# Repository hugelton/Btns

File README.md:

# Btns
Buttons board compatible with monome grid

## Overview
Btns is a clone of [Monome Grid]([url](https://monome.org)).

**⚠️ It doesn't support 16 levels of LED grey scale. It just turns on or off. **

## Make
### Hardware
Make your board from the gerber.

#### BOM
+ Raspberry Pi Pico (or same footprint clones) * 1
+ TSHD-T-2.8T2 SMD Tact switch with LED * 64
+ 1N4148WS (SOD-323) SMD diode * 64
+ TM1640 LED segments driver * 1
+ 10k THT resistor * 2
+ 10ohm THT resistor * 1
+ MPU-6050 (optional for tilt mod)
+ VXO7803-500 (optional)
+ Eurorack 16pin Bus Conn (optional)

### Firmware
upload the firmware to Pico from [Release]([url](https://github.com/hugelton/Btns/releases/tag/0.3)). 

### Test (on Norns)
Please use okyeron's [grid-test](https://github.com/okyeron/grid-test) 

```
;install https://github.com/okyeron/grid-test
```

### Plans
+ support MPU-6050 (tilt)
+ support multi-PWM
+ support other buttons

## Acknowledgments
Based on okyeron's [neotrellis-monome](https://github.com/okyeron/neotrellis-monome/) project.

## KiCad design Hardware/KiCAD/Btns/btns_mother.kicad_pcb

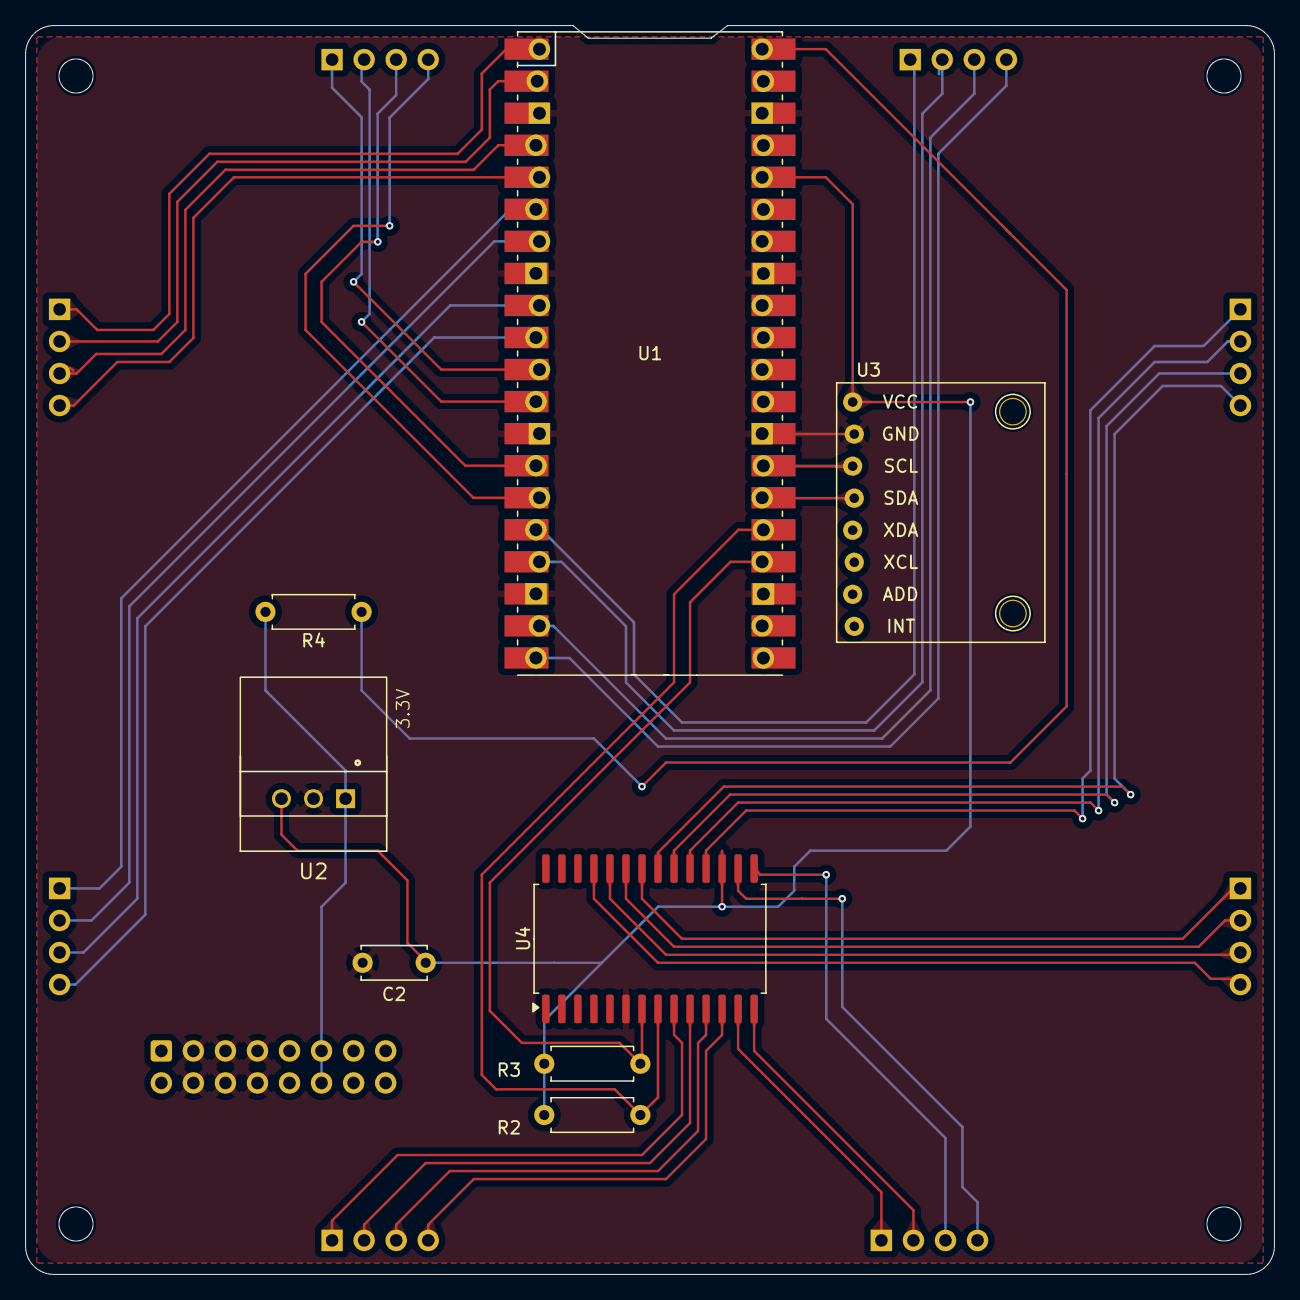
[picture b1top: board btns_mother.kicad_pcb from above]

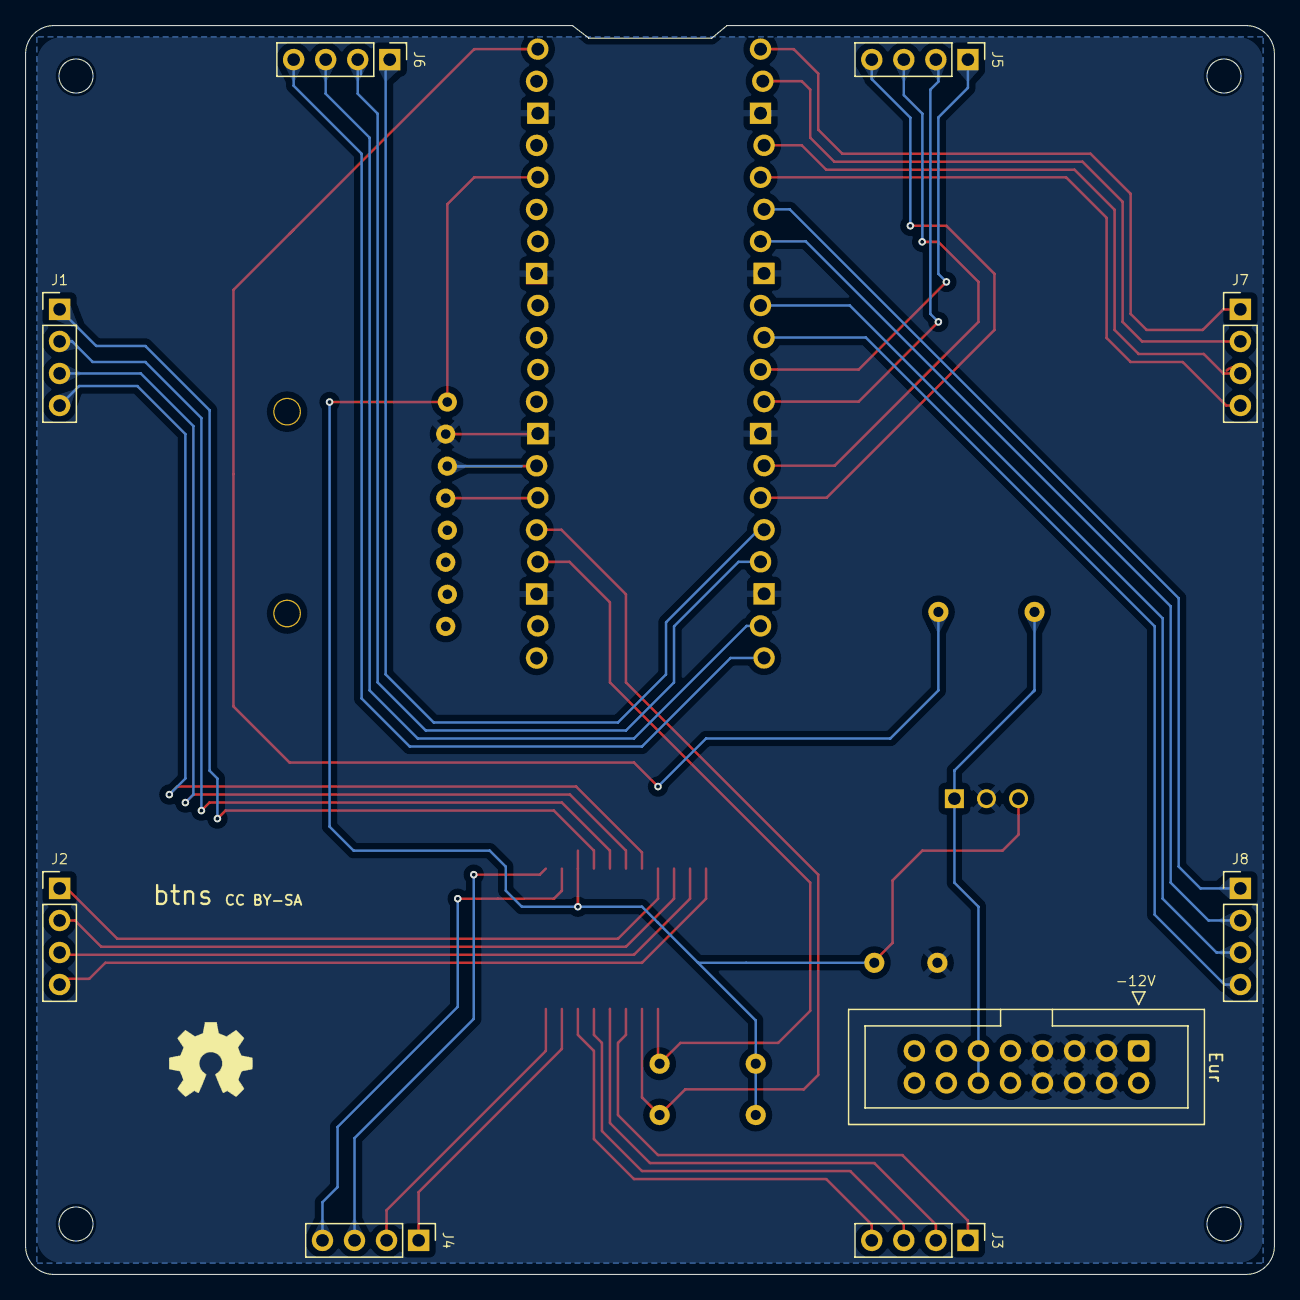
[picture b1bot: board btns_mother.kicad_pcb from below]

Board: 2 copper layers, 99.0 x 99.0 mm, 17 parts (9 on the bottom side), 40 nets.

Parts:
C2: 10uF; C_Disc_D5.0mm_W2.5mm_P5.00mm
Eur: IDC-Header_2x08_P2.54mm_Vertical
J1, J2, J3, J4, J5, J6, J7, J8: Conn_01x04_Pin; PinHeader_1x04_P2.54mm_Vertical
R2, R3: 10k; R_Axial_DIN0207_L6.3mm_D2.5mm_P7.62mm_Horizontal
R4: 10; R_Axial_DIN0207_L6.3mm_D2.5mm_P7.62mm_Horizontal
U1: Pico; RPi_Pico
U2: VX78_O78
U3: module_mpu6050
U4: TM1640; SOP-28_8.4x18.16mm_P1.27mm

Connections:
+3V3: C2.1, R2.1, R3.1, U1.36 (3V3), U2.3 (+VOUT/GND), U3.1 (VCC), U4.17 (VDD)
GND: C2.2, Eur.3, Eur.4, Eur.5, Eur.6, Eur.7, Eur.8, U1.3 (GND), U1.8 (GND), U1.13 (GND), U1.18 (GND), U1.23 (GND), U1.28 (GND), U1.33 (AGND), U1.38 (GND), U2.2 (GND/-VOUT), U3.2 (GND), U4.6 (VSS)
I2C0_SCL: U1.27 (GPIO21), U3.3 (SCL)
I2C0_SDA: U1.26 (GPIO20), U3.4 (SDA)
LED_COL_1: J3.1, U4.9 (SEG1)
LED_COL_2: J3.2, U4.10 (SEG2)
LED_COL_3: J3.3, U4.11 (SEG3)
LED_COL_4: J3.4, U4.12 (SEG4)
LED_COL_5: J4.1, U4.13 (SEG5)
LED_COL_6: J4.2, U4.14 (SEG6)
LED_COL_7: J4.3, U4.15 (SEG7)
LED_COL_8: J4.4, U4.16 (SEG8)
LED_ROW_1: J1.1, U4.18 (GRID1)
LED_ROW_2: J1.2, U4.19 (GRID2)
LED_ROW_3: J1.3, U4.20 (GRID3)
LED_ROW_4: J1.4, U4.21 (GRID4)
LED_ROW_5: J2.1, U4.22 (GRID5)
LED_ROW_6: J2.2, U4.23 (GRID6)
LED_ROW_7: J2.3, U4.24 (GRID7)
LED_ROW_8: J2.4, U4.25 (GRID8)
unnamed: Eur.11, Eur.12, R4.2, U2.1 (+VIN)
SW_COL_1: J5.1, U1.11 (GPIO8)
SW_COL_2: J5.2, U1.12 (GPIO9)
SW_COL_3: J5.3, U1.14 (GPIO10)
SW_COL_4: J5.4, U1.15 (GPIO11)
SW_COL_5: J6.1, U1.16 (GPIO12)
SW_COL_6: J6.2, U1.17 (GPIO13)
SW_COL_7: J6.3, U1.19 (GPIO14)
SW_COL_8: J6.4, U1.20 (GPIO15)
SW_ROW_1: J7.1, U1.1 (GPIO0)
SW_ROW_2: J7.2, U1.2 (GPIO1)
SW_ROW_3: J7.3, U1.4 (GPIO2)
SW_ROW_4: J7.4, U1.5 (GPIO3)
SW_ROW_5: J8.1, U1.6 (GPIO4)
SW_ROW_6: J8.2, U1.7 (GPIO5)
SW_ROW_7: J8.3, U1.9 (GPIO6)
SW_ROW_8: J8.4, U1.10 (GPIO7)
TM_D: R3.2, U1.24 (GPIO18), U4.7 (DIN)
TM_SCLK: R2.2, U1.25 (GPIO19), U4.8 (SCLK)
VBUS: R4.1, U1.40 (VBUS)

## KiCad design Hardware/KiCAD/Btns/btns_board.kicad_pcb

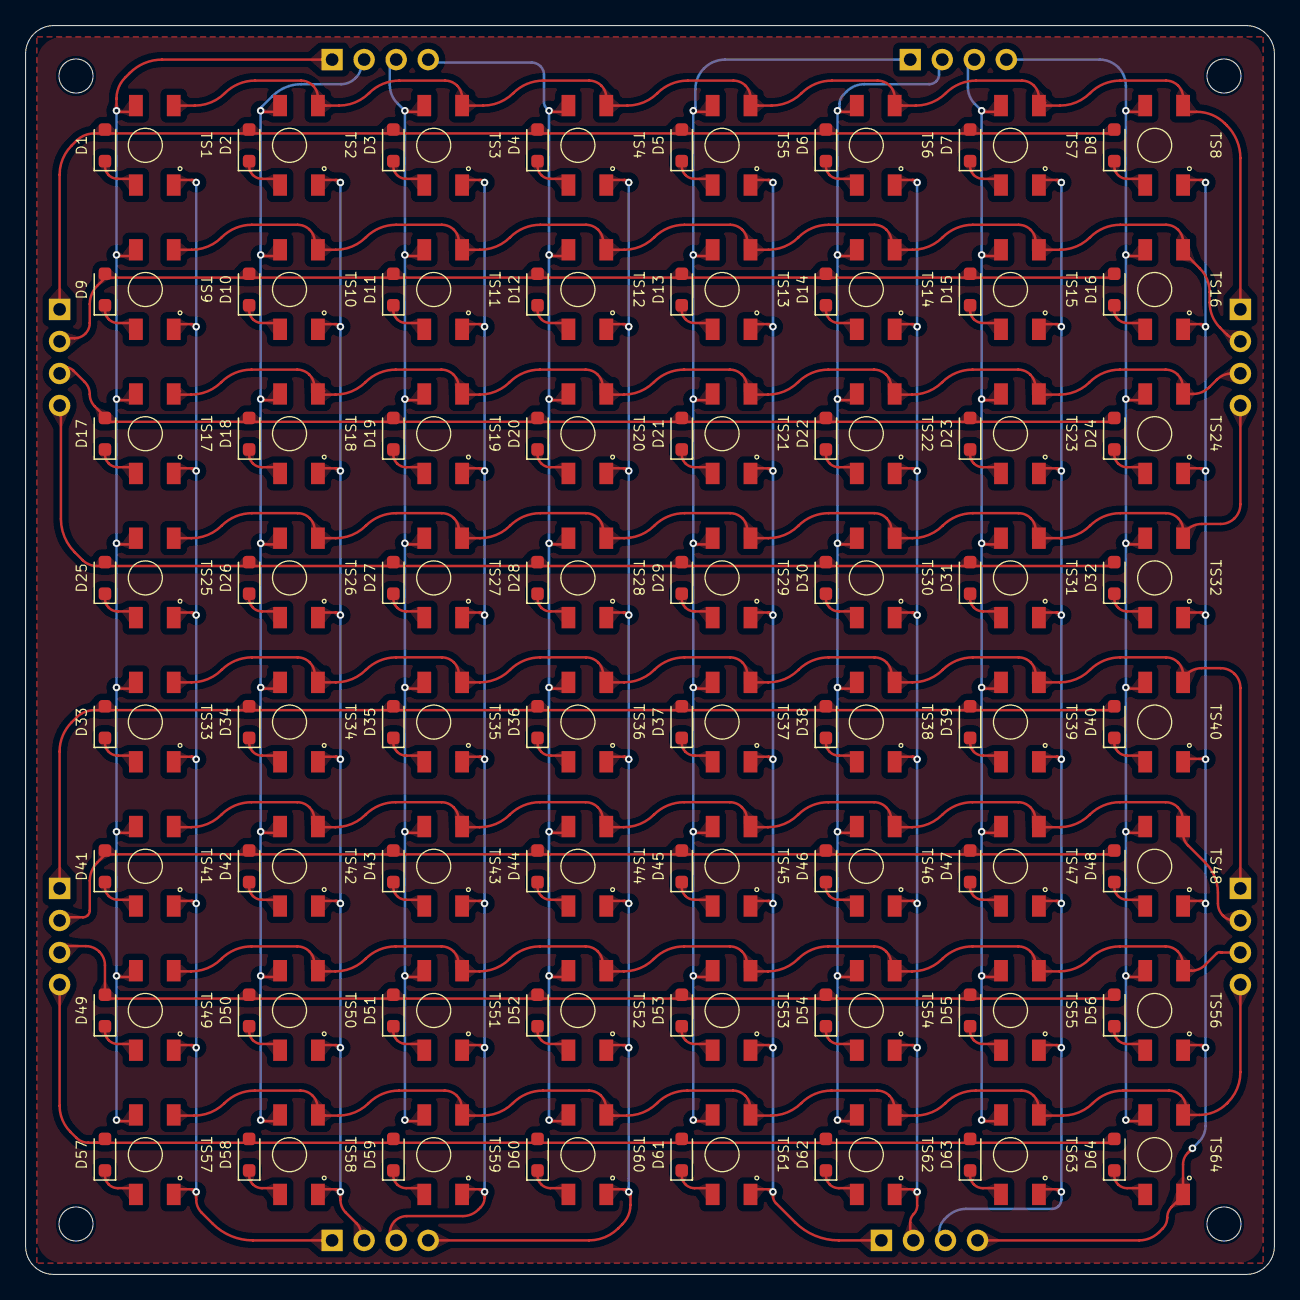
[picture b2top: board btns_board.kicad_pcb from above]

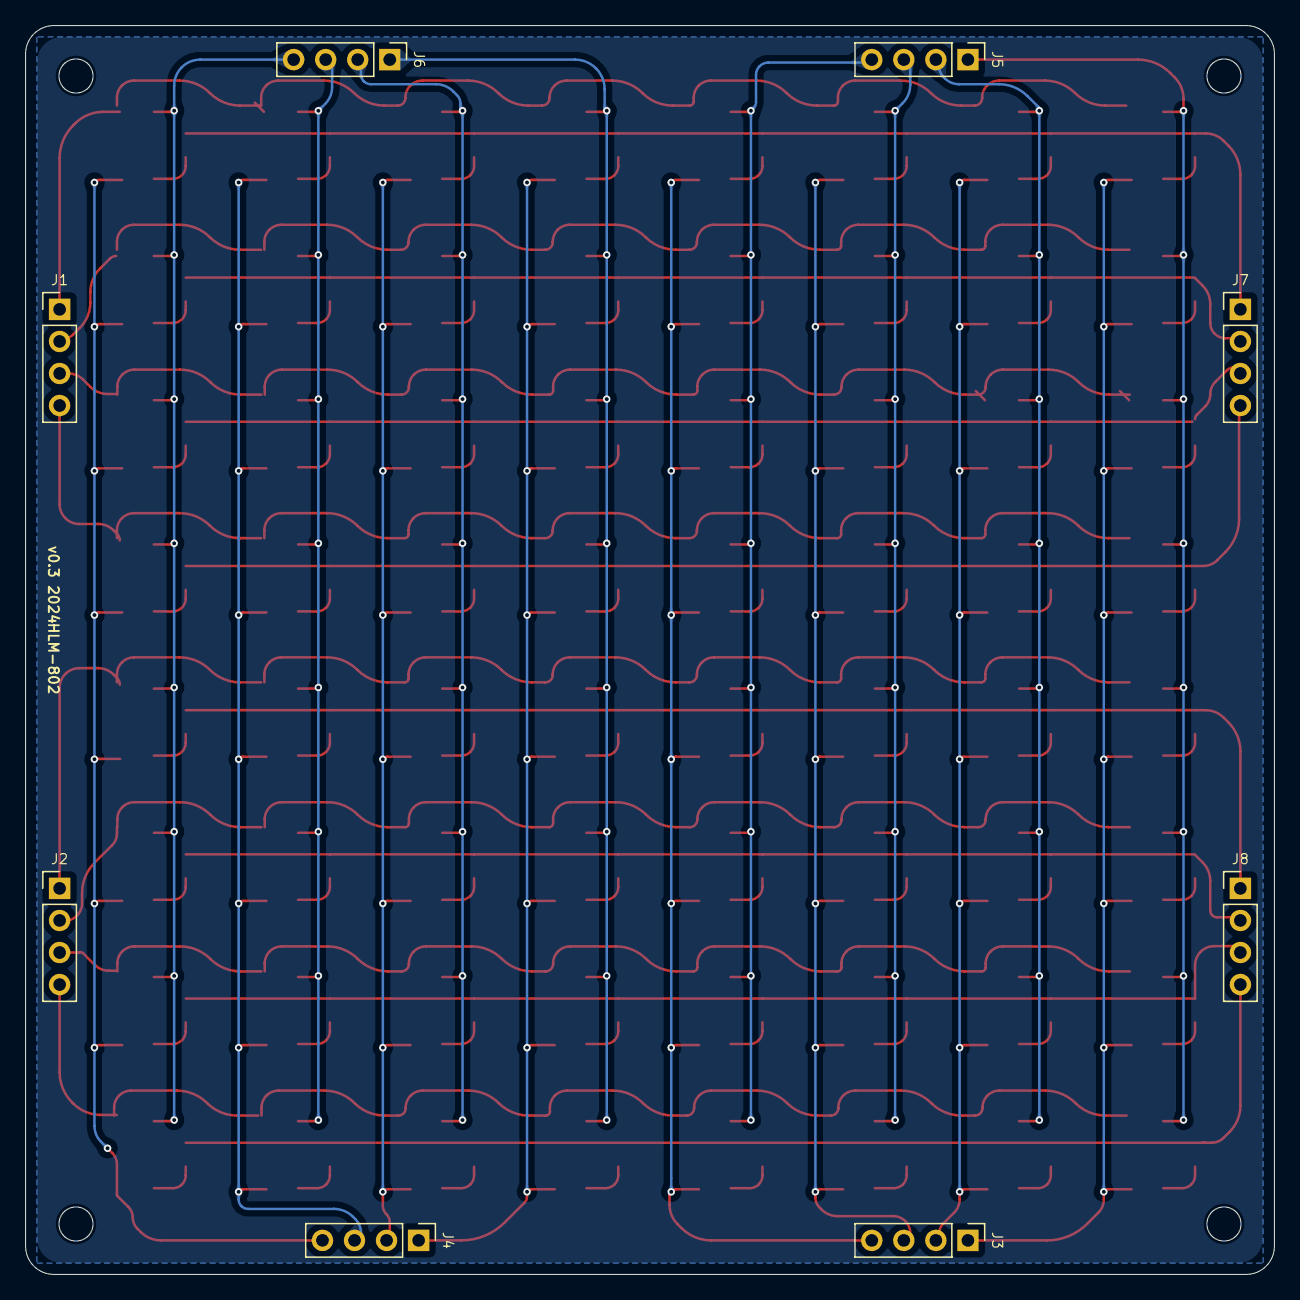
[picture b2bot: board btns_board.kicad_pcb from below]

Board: 2 copper layers, 99.0 x 99.0 mm, 136 parts (8 on the bottom side), 96 nets.

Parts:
D1, D2, D3, D4, D5, D6, D7, D8, D9, D10, D11, D12, D13, D14, D15, D16, D17, D18, D19, D20, D21, D22, D23, D24, D25, D26, D27, D28, D29, D30, D31, D32, D33, D34, D35, D36, D37, D38, D39, D40, D41, D42, D43, D44, D45, D46, D47, D48, D49, D50, D51, D52, D53, D54, D55, D56, D57, D58, D59, D60, D61, D62, D63, D64: 1N4148WS; D_SOD-323_HandSoldering
J1, J2, J3, J4, J5, J6, J7, J8: Conn_01x04_Pin; PinHeader_1x04_P2.54mm_Vertical
TS1, TS2, TS3, TS4, TS5, TS6, TS7, TS8, TS9, TS10, TS11, TS12, TS13, TS14, TS15, TS16, TS17, TS18, TS19, TS20, TS21, TS22, TS23, TS24, TS25, TS26, TS27, TS28, TS29, TS30, TS31, TS32, TS33, TS34, TS35, TS36, TS37, TS38, TS39, TS40, TS41, TS42, TS43, TS44, TS45, TS46, TS47, TS48, TS49, TS50, TS51, TS52, TS53, TS54, TS55, TS56, TS57, TS58, TS59, TS60, TS61, TS62, TS63, TS64: TSHD-T-2.8T2--6H

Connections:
LED_COL_1: J3.1, TS1.3 (L1), TS9.3 (L1), TS17.3 (L1), TS25.3 (L1), TS33.3 (L1), TS41.3 (L1), TS49.3 (L1), TS57.3 (L1)
LED_COL_2: J3.2, TS2.3 (L1), TS10.3 (L1), TS18.3 (L1), TS26.3 (L1), TS34.3 (L1), TS42.3 (L1), TS50.3 (L1), TS58.3 (L1)
LED_COL_3: J3.3, TS3.3 (L1), TS11.3 (L1), TS19.3 (L1), TS27.3 (L1), TS35.3 (L1), TS43.3 (L1), TS51.3 (L1), TS59.3 (L1)
LED_COL_4: J3.4, TS4.3 (L1), TS12.3 (L1), TS20.3 (L1), TS28.3 (L1), TS36.3 (L1), TS44.3 (L1), TS52.3 (L1), TS60.3 (L1)
LED_COL_5: J4.1, TS5.3 (L1), TS13.3 (L1), TS21.3 (L1), TS29.3 (L1), TS37.3 (L1), TS45.3 (L1), TS53.3 (L1), TS61.3 (L1)
LED_COL_6: J4.2, TS6.3 (L1), TS14.3 (L1), TS22.3 (L1), TS30.3 (L1), TS38.3 (L1), TS46.3 (L1), TS54.3 (L1), TS62.3 (L1)
LED_COL_7: J4.3, TS7.3 (L1), TS15.3 (L1), TS23.3 (L1), TS31.3 (L1), TS39.3 (L1), TS47.3 (L1), TS55.3 (L1), TS63.3 (L1)
LED_COL_8: J4.4, TS8.3 (L1), TS16.3 (L1), TS24.3 (L1), TS32.3 (L1), TS40.3 (L1), TS48.3 (L1), TS56.3 (L1), TS64.3 (L1)
LED_ROW_1: J1.1, TS1.4 (L2), TS2.4 (L2), TS3.4 (L2), TS4.4 (L2), TS5.4 (L2), TS6.4 (L2), TS7.4 (L2), TS8.4 (L2)
LED_ROW_2: J1.2, TS9.4 (L2), TS10.4 (L2), TS11.4 (L2), TS12.4 (L2), TS13.4 (L2), TS14.4 (L2), TS15.4 (L2), TS16.4 (L2)
LED_ROW_3: J1.3, TS17.4 (L2), TS18.4 (L2), TS19.4 (L2), TS20.4 (L2), TS21.4 (L2), TS22.4 (L2), TS23.4 (L2), TS24.4 (L2)
LED_ROW_4: J1.4, TS25.4 (L2), TS26.4 (L2), TS27.4 (L2), TS28.4 (L2), TS29.4 (L2), TS30.4 (L2), TS31.4 (L2), TS32.4 (L2)
LED_ROW_5: J2.1, TS33.4 (L2), TS34.4 (L2), TS35.4 (L2), TS36.4 (L2), TS37.4 (L2), TS38.4 (L2), TS39.4 (L2), TS40.4 (L2)
LED_ROW_6: J2.2, TS41.4 (L2), TS42.4 (L2), TS43.4 (L2), TS44.4 (L2), TS45.4 (L2), TS46.4 (L2), TS47.4 (L2), TS48.4 (L2)
LED_ROW_7: J2.3, TS49.4 (L2), TS50.4 (L2), TS51.4 (L2), TS52.4 (L2), TS53.4 (L2), TS54.4 (L2), TS55.4 (L2), TS56.4 (L2)
LED_ROW_8: J2.4, TS57.4 (L2), TS58.4 (L2), TS59.4 (L2), TS60.4 (L2), TS61.4 (L2), TS62.4 (L2), TS63.4 (L2), TS64.4 (L2)
unnamed: D1.1 (K), TS1.1
unnamed: D2.1 (K), TS2.1
unnamed: D3.1 (K), TS3.1
unnamed: D4.1 (K), TS4.1
unnamed: D5.1 (K), TS5.1
unnamed: D6.1 (K), TS6.1
unnamed: D7.1 (K), TS7.1
unnamed: D8.1 (K), TS8.1
unnamed: D9.1 (K), TS9.1
unnamed: D10.1 (K), TS10.1
unnamed: D11.1 (K), TS11.1
unnamed: D12.1 (K), TS12.1
unnamed: D13.1 (K), TS13.1
unnamed: D14.1 (K), TS14.1
unnamed: D15.1 (K), TS15.1
unnamed: D16.1 (K), TS16.1
unnamed: D17.1 (K), TS17.1
unnamed: D18.1 (K), TS18.1
unnamed: D19.1 (K), TS19.1
unnamed: D20.1 (K), TS20.1
unnamed: D21.1 (K), TS21.1
unnamed: D22.1 (K), TS22.1
unnamed: D23.1 (K), TS23.1
unnamed: D24.1 (K), TS24.1
unnamed: D25.1 (K), TS25.1
unnamed: D26.1 (K), TS26.1
unnamed: D27.1 (K), TS27.1
unnamed: D28.1 (K), TS28.1
unnamed: D29.1 (K), TS29.1
unnamed: D30.1 (K), TS30.1
unnamed: D31.1 (K), TS31.1
unnamed: D32.1 (K), TS32.1
unnamed: D33.1 (K), TS33.1
unnamed: D34.1 (K), TS34.1
unnamed: D35.1 (K), TS35.1
unnamed: D36.1 (K), TS36.1
unnamed: D37.1 (K), TS37.1
unnamed: D38.1 (K), TS38.1
unnamed: D39.1 (K), TS39.1
unnamed: D40.1 (K), TS40.1
unnamed: D41.1 (K), TS41.1
unnamed: D42.1 (K), TS42.1
unnamed: D43.1 (K), TS43.1
unnamed: D44.1 (K), TS44.1
unnamed: D45.1 (K), TS45.1
unnamed: D46.1 (K), TS46.1
unnamed: D47.1 (K), TS47.1
unnamed: D48.1 (K), TS48.1
unnamed: D49.1 (K), TS49.1
unnamed: D50.1 (K), TS50.1
unnamed: D51.1 (K), TS51.1
unnamed: D52.1 (K), TS52.1
unnamed: D53.1 (K), TS53.1
unnamed: D54.1 (K), TS54.1
unnamed: D55.1 (K), TS55.1
unnamed: D56.1 (K), TS56.1
unnamed: D57.1 (K), TS57.1
unnamed: D58.1 (K), TS58.1
unnamed: D59.1 (K), TS59.1
unnamed: D60.1 (K), TS60.1
unnamed: D61.1 (K), TS61.1
unnamed: D62.1 (K), TS62.1
unnamed: D63.1 (K), TS63.1
unnamed: D64.1 (K), TS64.1
SW_COL_1: J5.1, TS1.2, TS9.2, TS17.2, TS25.2, TS33.2, TS41.2, TS49.2, TS57.2
SW_COL_2: J5.2, TS2.2, TS10.2, TS18.2, TS26.2, TS34.2, TS42.2, TS50.2, TS58.2
SW_COL_3: J5.3, TS3.2, TS11.2, TS19.2, TS27.2, TS35.2, TS43.2, TS51.2, TS59.2
SW_COL_4: J5.4, TS4.2, TS12.2, TS20.2, TS28.2, TS36.2, TS44.2, TS52.2, TS60.2
SW_COL_5: J6.1, TS5.2, TS13.2, TS21.2, TS29.2, TS37.2, TS45.2, TS53.2, TS61.2
SW_COL_6: J6.2, TS6.2, TS14.2, TS22.2, TS30.2, TS38.2, TS46.2, TS54.2, TS62.2
SW_COL_7: J6.3, TS7.2, TS15.2, TS23.2, TS31.2, TS39.2, TS47.2, TS55.2, TS63.2
SW_COL_8: J6.4, TS8.2, TS16.2, TS24.2, TS32.2, TS40.2, TS48.2, TS56.2, TS64.2
SW_ROW_1: D1.2 (A), D2.2 (A), D3.2 (A), D4.2 (A), D5.2 (A), D6.2 (A), D7.2 (A), D8.2 (A), J7.1
SW_ROW_2: D9.2 (A), D10.2 (A), D11.2 (A), D12.2 (A), D13.2 (A), D14.2 (A), D15.2 (A), D16.2 (A), J7.2
SW_ROW_3: D17.2 (A), D18.2 (A), D19.2 (A), D20.2 (A), D21.2 (A), D22.2 (A), D23.2 (A), D24.2 (A), J7.3
SW_ROW_4: D25.2 (A), D26.2 (A), D27.2 (A), D28.2 (A), D29.2 (A), D30.2 (A), D31.2 (A), D32.2 (A), J7.4
SW_ROW_5: D33.2 (A), D34.2 (A), D35.2 (A), D36.2 (A), D37.2 (A), D38.2 (A), D39.2 (A), D40.2 (A), J8.1
SW_ROW_6: D41.2 (A), D42.2 (A), D43.2 (A), D44.2 (A), D45.2 (A), D46.2 (A), D47.2 (A), D48.2 (A), J8.2
SW_ROW_7: D49.2 (A), D50.2 (A), D51.2 (A), D52.2 (A), D53.2 (A), D54.2 (A), D55.2 (A), D56.2 (A), J8.3
SW_ROW_8: D57.2 (A), D58.2 (A), D59.2 (A), D60.2 (A), D61.2 (A), D62.2 (A), D63.2 (A), D64.2 (A), J8.4

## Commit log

2024-09-10 upload hardware files
2024-09-12 Add KiCAD project
2024-10-10 Update Btns_Pico.ino
    Fix flip led matrix
2024-10-19 Support tilt (beta)

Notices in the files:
Hardware/KiCAD/Btns/btns_mother.kicad_pcb:
CC BY-SA
